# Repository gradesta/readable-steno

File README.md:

# readable-steno

[Discord link](https://discord.com/channels/136953735426473984/1390298469813452810)

Imagine if you had a steno keyboard where the keys could move on their own. This would allow you to read haptically in the same way you typed. And perhapse at up to hundres of words per minute. Far faster than braille. This is the idea of our project. 

So far we have a prototype with LED lights rather than solenoids. In the future, we will replace these LEDs with electromagnets which can trigger the keys to jump up at you.

# Tutorial to replicate
### Prerquisites
There are some dependencies you will have to install before following this tutorial, these include dependencies both for the firmware and pico-sdk:
```
sudo apt install cmake python3 build-essential gcc-arm-none-eabi libnewlib-arm-none-eabi libstdc++-arm-none-eabi-newlib
```
### Steps
1. Clone [the readable steno](https://github.com/gradesta/readable-steno#) and the [pico-sdk](https://github.com/raspberrypi/pico-sdk#) repositories: 
```
git clone git@github.com:gradesta/readable-steno.git
git clone git@github.com:raspberrypi/pico-sdk.git
```
2. Now we need to initiate the submodules, for pico-sdk as the tinyUsb module does not come installed in pico-sdk immediately:
```
cd pico-sdk
git submodule update --init
```

3. Before we can start building our project, we need a `dict.h` file, which the firmware expects to be present. To do this, we will use a .json steno dictionary. You can either use the same as us (typey-type-full.json) or add your own in its place. We will move to the `read_code` folder and run the translation script:
```
cd ../readable-steno/read_code
python3 translator.py <your_dict_name>.json
```
For example 
```
python3 translator.py typey-type-full.json
```
You should see a `dict.h` file now.

4. Next we will make a build folder and generate the necessary CMake files in it. If you are correctly following these steps, then the file paths should be the same:
```
mkdir build
cd build
cmake .. -DPICO_SDK_PATH=../../../pico-sdk
```

5. You should have several new files generated in the `build` folder. Now, just run:
```
make
```
And your firmware should be compiled.

6. After it is compiled a file called `read_code.uf2` will be in the `build` folder. This is the firmware for the board. To flash it, hold the reset button on the microcontroller while plugging it in. It should show up as a usb device. Now just drag the `read_code.uf2` file on it, wait while it flashes and you are done.

### Keep in mind
If you used the liatris  controller, then you cannot use GPIO 10 for the LEDs. In [this](https://github.com/gradesta/readable-steno/blob/main/dev_log/%235-11_08_2025-15_08_2025.md) dev-log we showed how we fixed it. The important thing is, not to forget to change the pin number in [led_driver.h](https://github.com/gradesta/readable-steno/blob/main/read_code/led_driver.h). 

## Testing
To actually test the software, you will need some kind of serial monitor, for exapmle `screen` and find the com port of the keyboard. In our case it was /dev/ttyACM0. Now you just run:
```
sudo screen /dev/ttyACM0 115200
```
And a serial monitor should show up where you can type a message to show on the keyboard (up to 3000 characters)

https://github.com/user-attachments/assets/7c71d7f1-2565-4da7-bef9-faf2f1da297b

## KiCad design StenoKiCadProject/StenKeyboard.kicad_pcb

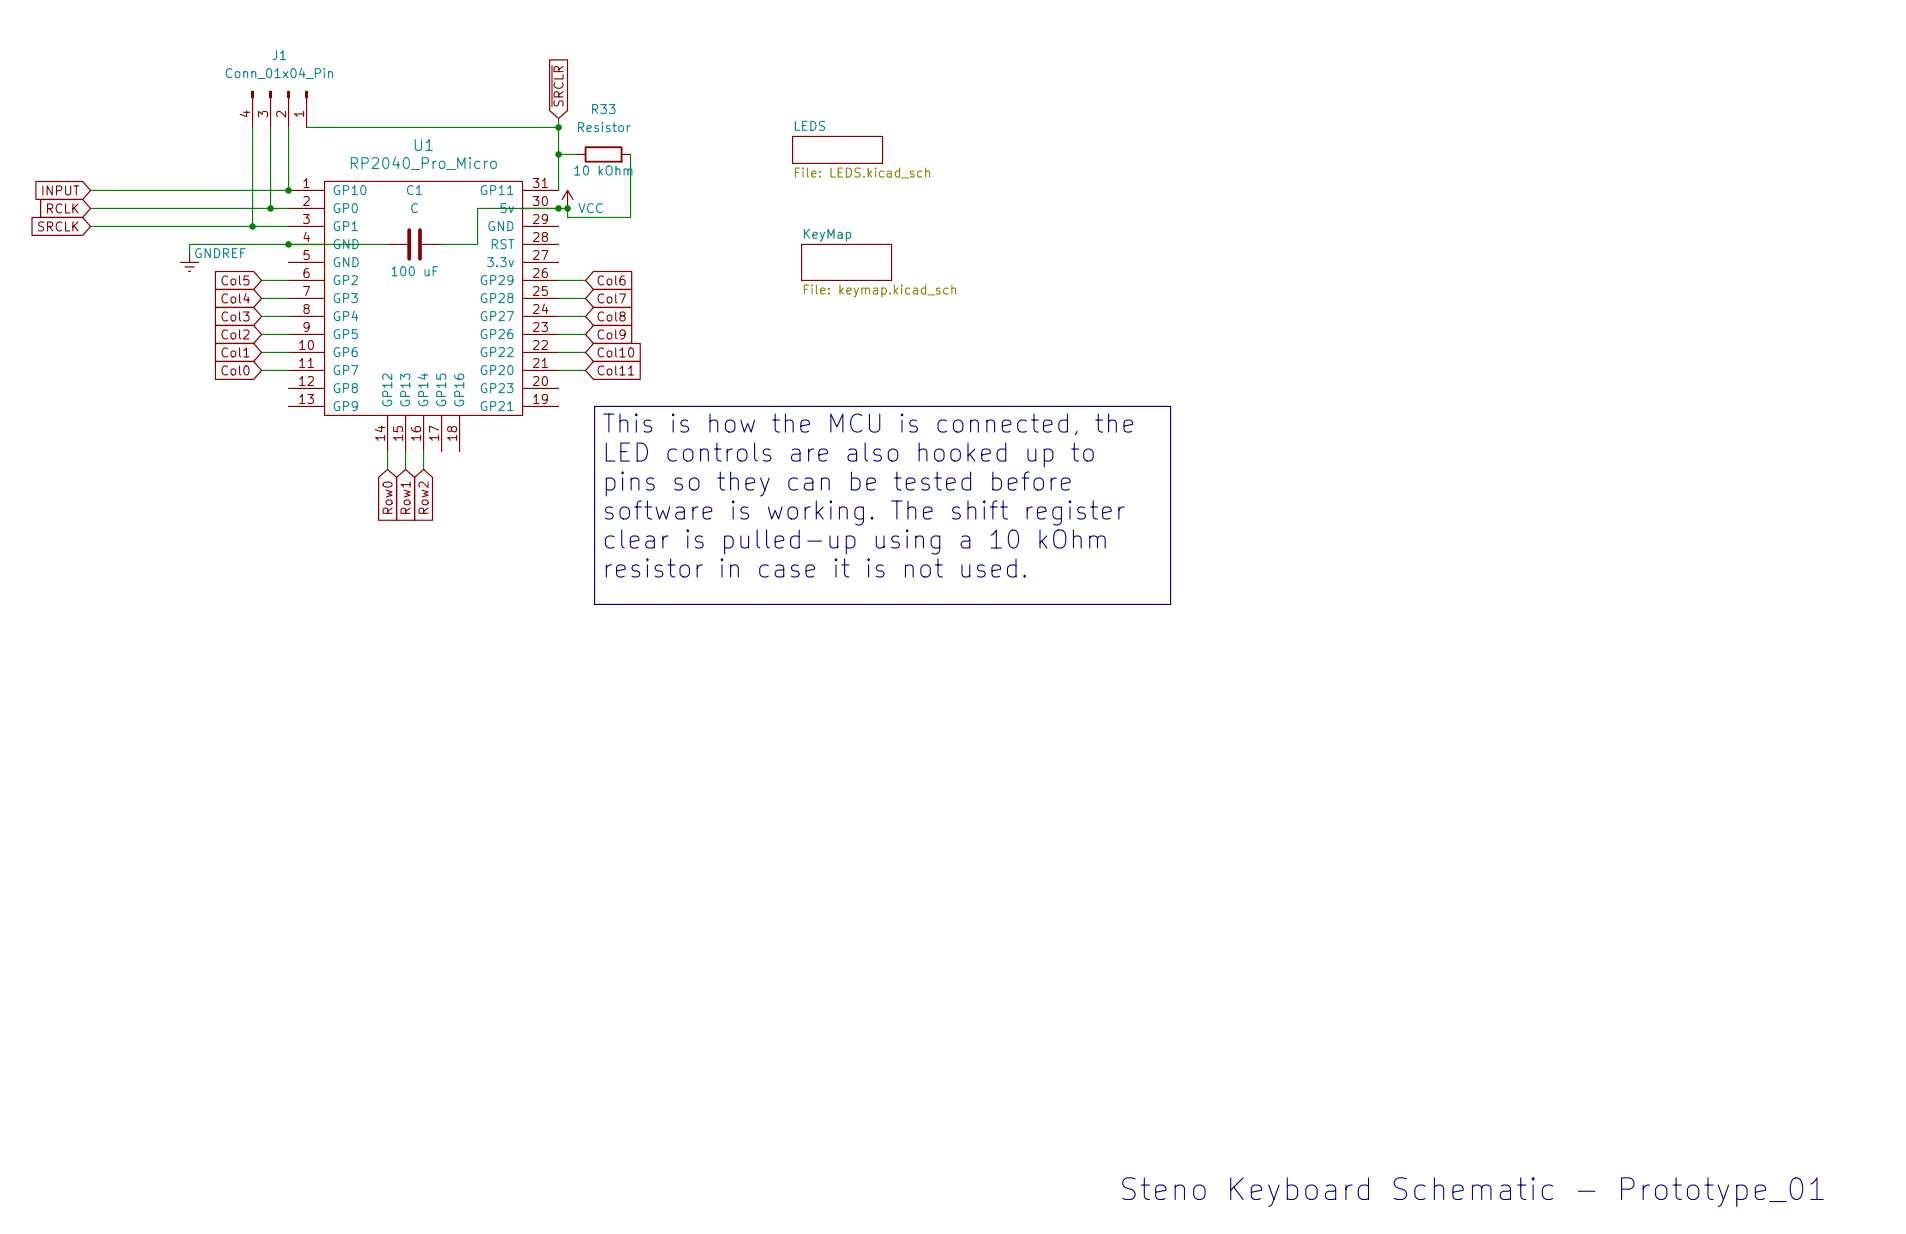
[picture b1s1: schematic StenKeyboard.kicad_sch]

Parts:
C1: C; C_1206_3216Metric
J1: Conn_01x04_Pin; PinHeader_1x04_P2.54mm_Vertical
R33: Resistor; R_1206_3216Metric
U1: RP2040_Pro_Micro

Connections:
Col0: U1.11 (GP7); also elsewhere on the board
Col1: U1.10 (GP6); also elsewhere on the board
Col2: U1.9 (GP5); also elsewhere on the board
Col3: U1.8 (GP4); also elsewhere on the board
Col4: U1.7 (GP3); also elsewhere on the board
Col5: U1.6 (GP2); also elsewhere on the board
Col6: U1.26 (GP29); also elsewhere on the board
Col7: U1.25 (GP28); also elsewhere on the board
Col8: U1.24 (GP27); also elsewhere on the board
Col9: U1.23 (GP26); also elsewhere on the board
Col10: U1.22 (GP22); also elsewhere on the board
Col11: U1.21 (GP20); also elsewhere on the board
GNDREF: C1.1, U1.4 (GND); also elsewhere on the board
INPUT: J1.2, U1.1 (GP10); also elsewhere on the board
RCLK: J1.3, U1.2 (GP0); also elsewhere on the board
Row0: U1.14 (GP12); also elsewhere on the board
Row1: U1.15 (GP13); also elsewhere on the board
Row2: U1.16 (GP14); also elsewhere on the board
SRCLK: J1.4, U1.3 (GP1); also elsewhere on the board
VCC: C1.2, R33.2, U1.30 (5v); also elsewhere on the board
~SRCLR: J1.1, R33.1, U1.31 (GP11); also elsewhere on the board

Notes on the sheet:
Steno Keyboard Schematic - Prototype_01
This is how the MCU is connected, the LED controls are also hooked up to pins so they can be tested before software is working. The shift register clear is pulled-up using a 10 kOhm resistor in case it is not used.

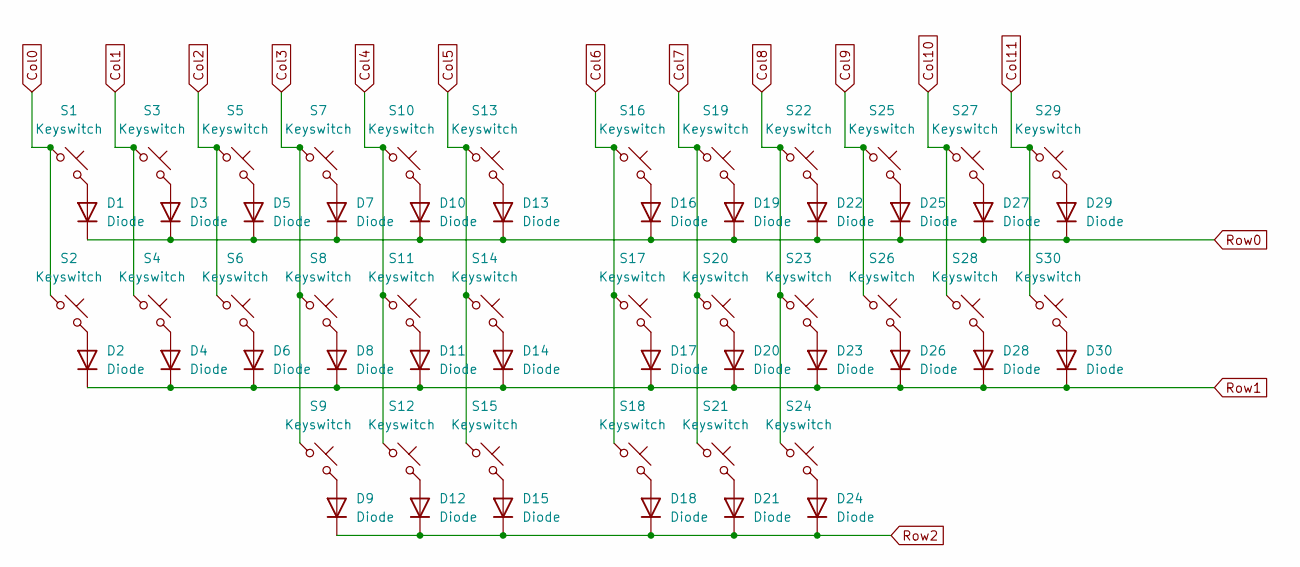
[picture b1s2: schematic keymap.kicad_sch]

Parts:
D1, D2, D3, D4, D5, D6, D7, D8, D9, D10, D11, D12, D13, D14, D15, D16, D17, D18, D19, D20, D21, D22, D23, D24, D25, D26, D27, D28, D29, D30: Diode; D_1206_3216Metric
S1, S2, S3, S4, S5, S6, S7, S8, S9, S10, S11, S12, S13, S14, S15, S16, S17, S18, S19, S20, S21, S22, S23, S24, S25, S26, S27, S28, S29, S30: Keyswitch; Hotswap_Choc_V1

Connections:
Col0: S1.1, S2.1; also elsewhere on the board
Col1: S3.1, S4.1; also elsewhere on the board
Col2: S5.1, S6.1; also elsewhere on the board
Col3: S7.1, S8.1, S9.1; also elsewhere on the board
Col4: S10.1, S11.1, S12.1; also elsewhere on the board
Col5: S13.1, S14.1, S15.1; also elsewhere on the board
Col6: S16.1, S17.1, S18.1; also elsewhere on the board
Col7: S19.1, S20.1, S21.1; also elsewhere on the board
Col8: S22.1, S23.1, S24.1; also elsewhere on the board
Col9: S25.1, S26.1; also elsewhere on the board
Col10: S27.1, S28.1; also elsewhere on the board
Col11: S29.1, S30.1; also elsewhere on the board
unnamed: D1.2 (A), S1.2
unnamed: D2.2 (A), S2.2
unnamed: D3.2 (A), S3.2
unnamed: D4.2 (A), S4.2
unnamed: D5.2 (A), S5.2
unnamed: D6.2 (A), S6.2
unnamed: D7.2 (A), S7.2
unnamed: D8.2 (A), S8.2
unnamed: D9.2 (A), S9.2
unnamed: D10.2 (A), S10.2
unnamed: D11.2 (A), S11.2
unnamed: D12.2 (A), S12.2
unnamed: D13.2 (A), S13.2
unnamed: D14.2 (A), S14.2
unnamed: D15.2 (A), S15.2
unnamed: D16.2 (A), S16.2
unnamed: D17.2 (A), S17.2
unnamed: D18.2 (A), S18.2
unnamed: D19.2 (A), S19.2
unnamed: D20.2 (A), S20.2
unnamed: D21.2 (A), S21.2
unnamed: D22.2 (A), S22.2
unnamed: D23.2 (A), S23.2
unnamed: D24.2 (A), S24.2
unnamed: D25.2 (A), S25.2
unnamed: D26.2 (A), S26.2
unnamed: D27.2 (A), S27.2
unnamed: D28.2 (A), S28.2
unnamed: D29.2 (A), S29.2
unnamed: D30.2 (A), S30.2
Row0: D1.1 (K), D3.1 (K), D5.1 (K), D7.1 (K), D10.1 (K), D13.1 (K), D16.1 (K), D19.1 (K), D22.1 (K), D25.1 (K), D27.1 (K), D29.1 (K); also elsewhere on the board
Row1: D2.1 (K), D4.1 (K), D6.1 (K), D8.1 (K), D11.1 (K), D14.1 (K), D17.1 (K), D20.1 (K), D23.1 (K), D26.1 (K), D28.1 (K), D30.1 (K); also elsewhere on the board
Row2: D9.1 (K), D12.1 (K), D15.1 (K), D18.1 (K), D21.1 (K), D24.1 (K); also elsewhere on the board

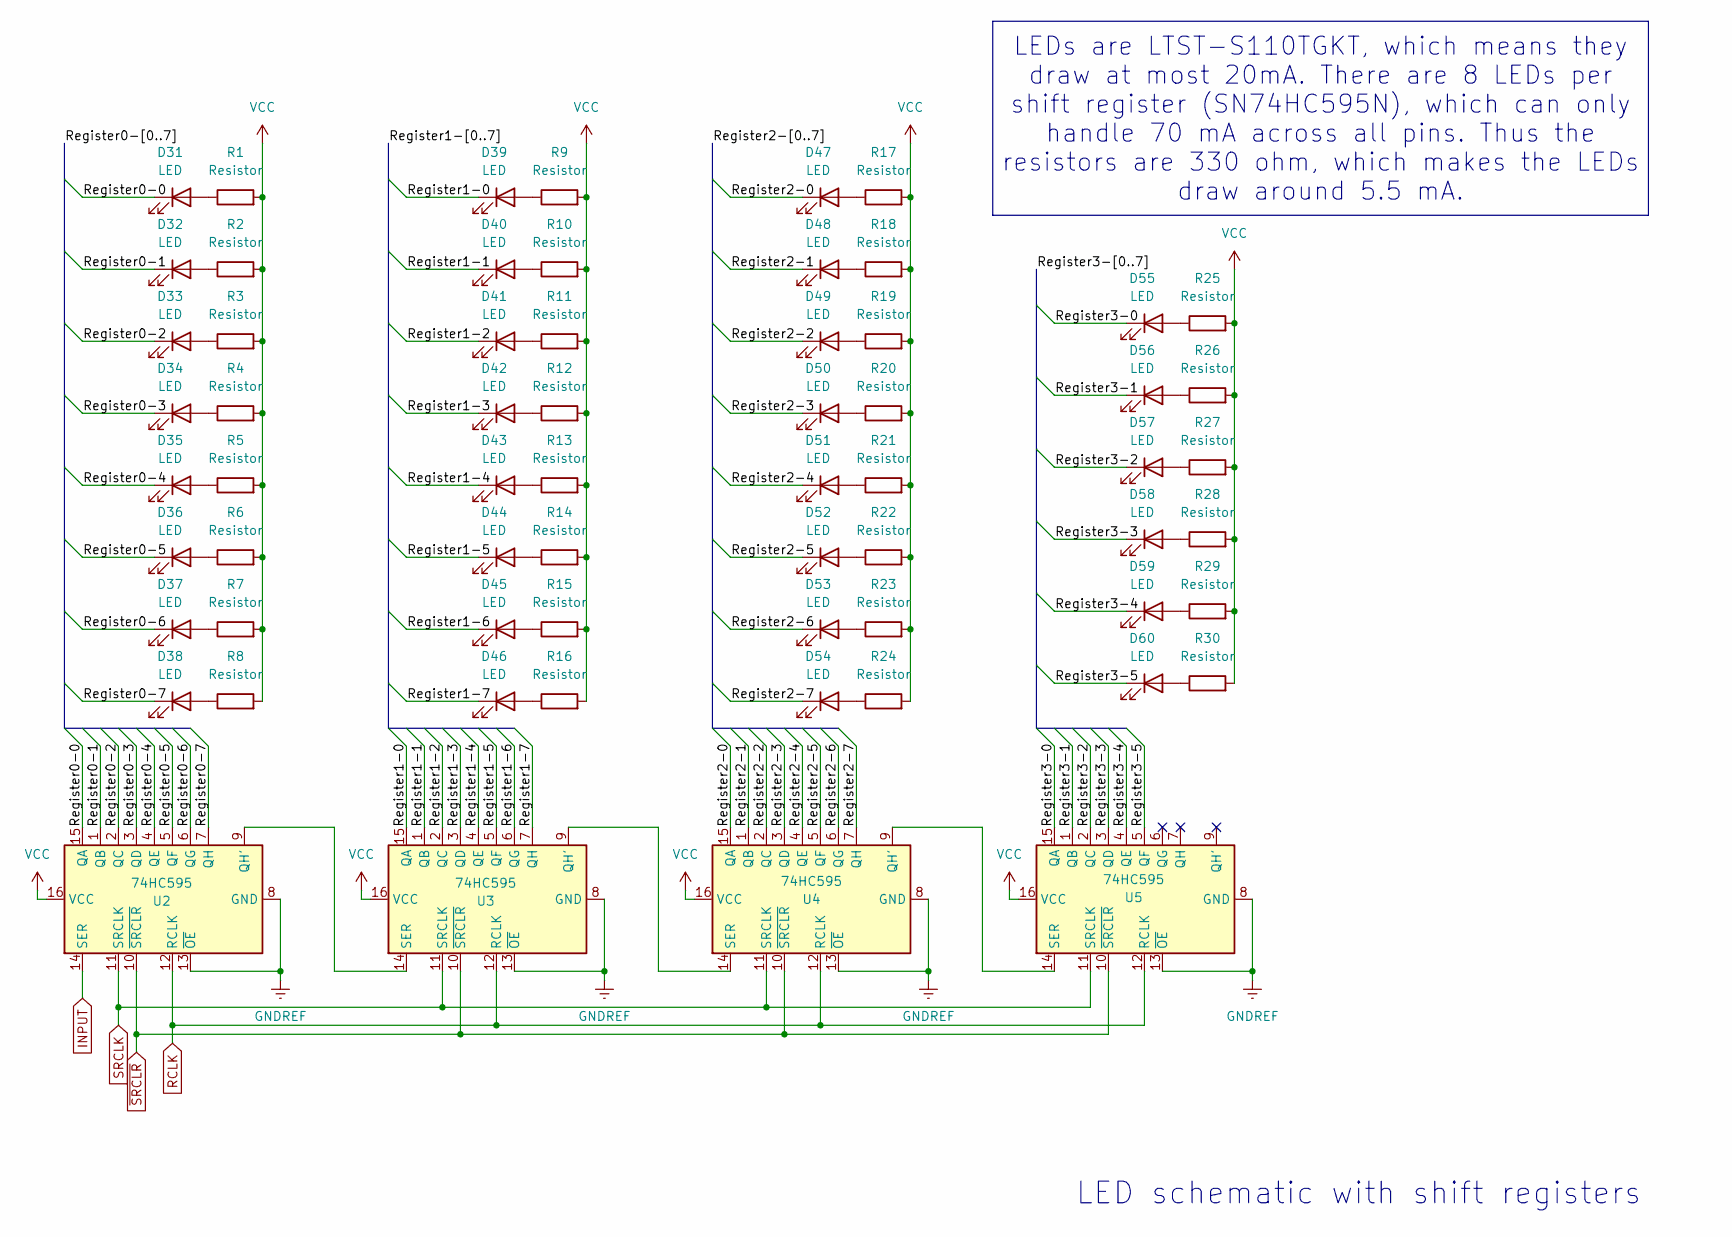
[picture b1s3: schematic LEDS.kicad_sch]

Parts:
D31, D32, D33, D34, D35, D36, D37, D38, D39, D40, D41, D42, D43, D44, D45, D46, D47, D48, D49, D50, D51, D52, D53, D54, D55, D56, D57, D58, D59, D60: LED; LED_1206_3216Metric
R1, R2, R3, R4, R5, R6, R7, R8, R9, R10, R11, R12, R13, R14, R15, R16, R17, R18, R19, R20, R21, R22, R23, R24, R25, R26, R27, R28, R29, R30: Resistor; R_1206_3216Metric
U2, U3, U4, U5: 74HC595; DIP-16_W7.62mm

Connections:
/LEDS/Register0-0: D31.1 (K), U2.15 (QA)
/LEDS/Register0-1: D32.1 (K), U2.1 (QB)
/LEDS/Register0-2: D33.1 (K), U2.2 (QC)
/LEDS/Register0-3: D34.1 (K), U2.3 (QD)
/LEDS/Register0-4: D35.1 (K), U2.4 (QE)
/LEDS/Register0-5: D36.1 (K), U2.5 (QF)
/LEDS/Register0-6: D37.1 (K), U2.6 (QG)
/LEDS/Register0-7: D38.1 (K), U2.7 (QH)
/LEDS/Register1-0: D39.1 (K), U3.15 (QA)
/LEDS/Register1-1: D40.1 (K), U3.1 (QB)
/LEDS/Register1-2: D41.1 (K), U3.2 (QC)
/LEDS/Register1-3: D42.1 (K), U3.3 (QD)
/LEDS/Register1-4: D43.1 (K), U3.4 (QE)
/LEDS/Register1-5: D44.1 (K), U3.5 (QF)
/LEDS/Register1-6: D45.1 (K), U3.6 (QG)
/LEDS/Register1-7: D46.1 (K), U3.7 (QH)
/LEDS/Register2-0: D47.1 (K), U4.15 (QA)
/LEDS/Register2-1: D48.1 (K), U4.1 (QB)
/LEDS/Register2-2: D49.1 (K), U4.2 (QC)
/LEDS/Register2-3: D50.1 (K), U4.3 (QD)
/LEDS/Register2-4: D51.1 (K), U4.4 (QE)
/LEDS/Register2-5: D52.1 (K), U4.5 (QF)
/LEDS/Register2-6: D53.1 (K), U4.6 (QG)
/LEDS/Register2-7: D54.1 (K), U4.7 (QH)
/LEDS/Register3-0: D55.1 (K), U5.15 (QA)
/LEDS/Register3-1: D56.1 (K), U5.1 (QB)
/LEDS/Register3-2: D57.1 (K), U5.2 (QC)
/LEDS/Register3-3: D58.1 (K), U5.3 (QD)
/LEDS/Register3-4: D59.1 (K), U5.4 (QE)
/LEDS/Register3-5: D60.1 (K), U5.5 (QF)
GNDREF: U2.8 (GND), U2.13 (~OE), U3.8 (GND), U3.13 (~OE), U4.8 (GND), U4.13 (~OE), U5.8 (GND), U5.13 (~OE); also elsewhere on the board
INPUT: U2.14 (SER); also elsewhere on the board
unnamed: D31.2 (A), R1.1
unnamed: D32.2 (A), R2.1
unnamed: D33.2 (A), R3.1
unnamed: D34.2 (A), R4.1
unnamed: D35.2 (A), R5.1
unnamed: D36.2 (A), R6.1
unnamed: D37.2 (A), R7.1
unnamed: D38.2 (A), R8.1
unnamed: D39.2 (A), R9.1
unnamed: D40.2 (A), R10.1
unnamed: D41.2 (A), R11.1
unnamed: D42.2 (A), R12.1
unnamed: D43.2 (A), R13.1
unnamed: D44.2 (A), R14.1
unnamed: D45.2 (A), R15.1
unnamed: D46.2 (A), R16.1
unnamed: D47.2 (A), R17.1
unnamed: D48.2 (A), R18.1
unnamed: D49.2 (A), R19.1
unnamed: D50.2 (A), R20.1
unnamed: D51.2 (A), R21.1
unnamed: D52.2 (A), R22.1
unnamed: D53.2 (A), R23.1
unnamed: D54.2 (A), R24.1
unnamed: D55.2 (A), R25.1
unnamed: D56.2 (A), R26.1
unnamed: D57.2 (A), R27.1
unnamed: D58.2 (A), R28.1
unnamed: D59.2 (A), R29.1
unnamed: D60.2 (A), R30.1
unnamed: U2.9 (QH'), U3.14 (SER)
unnamed: U3.9 (QH'), U4.14 (SER)
unnamed: U4.9 (QH'), U5.14 (SER)
RCLK: U2.12 (RCLK), U3.12 (RCLK), U4.12 (RCLK), U5.12 (RCLK); also elsewhere on the board
SRCLK: U2.11 (SRCLK), U3.11 (SRCLK), U4.11 (SRCLK), U5.11 (SRCLK); also elsewhere on the board
VCC: R1.2, R2.2, R3.2, R4.2, R5.2, R6.2, R7.2, R8.2, R9.2, R10.2, R11.2, R12.2, R13.2, R14.2, R15.2, R16.2, R17.2, R18.2, R19.2, R20.2, R21.2, R22.2, R23.2, R24.2, R25.2, R26.2, R27.2, R28.2, R29.2, R30.2, U2.16 (VCC), U3.16 (VCC), U4.16 (VCC), U5.16 (VCC); also elsewhere on the board
~SRCLR: U2.10 (~SRCLR), U3.10 (~SRCLR), U4.10 (~SRCLR), U5.10 (~SRCLR); also elsewhere on the board

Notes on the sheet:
LED schematic with shift registers
LEDs are LTST-S110TGKT, which means they draw at most 20mA. There are 8 LEDs per shift register (SN74HC595N), which can only handle 70 mA across all pins. Thus the resistors are 330 ohm, which makes the LEDs draw around 5.5 mA.

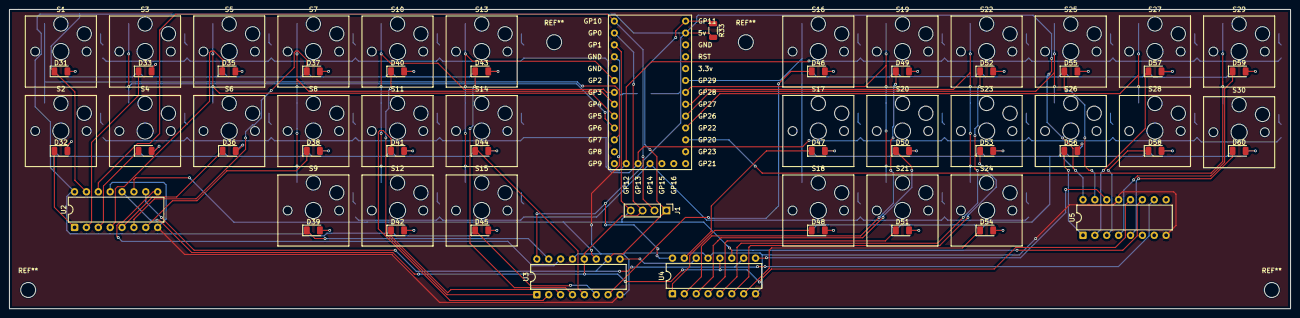
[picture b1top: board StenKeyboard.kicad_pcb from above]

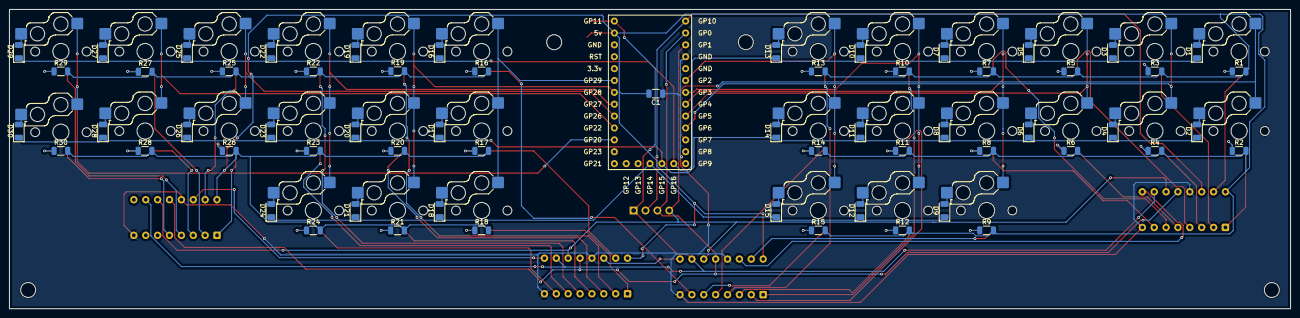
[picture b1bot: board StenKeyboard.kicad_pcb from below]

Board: 2 copper layers, 274.0 x 64.0 mm, 128 parts (61 on the bottom side), 114 nets.

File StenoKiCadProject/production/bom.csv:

Designator,Footprint,Quantity,Value,LCSC Part #
C1,1206,1,C,
"D1, D10, D11, D12, D13, D14, D15, D16, D17, D18, D19, D2, D20, D21, D22, D23, D24, D25, D26, D27, D28, D29, D3, D30, D4, D5, D6, D7, D8, D9",1206,30,Diode,
"D31, D32, D33, D34, D35, D36, D37, D38, D39, D40, D41, D42, D43, D44, D45, D46, D47, D48, D49, D50, D51, D52, D53, D54, D55, D56, D57, D58, D59, D60",1206,30,LED,
J1,PinHeader_1x04_P2.54mm_Vertical,1,Conn_01x04_Pin,
"R1, R10, R11, R12, R13, R14, R15, R16, R17, R18, R19, R2, R20, R21, R22, R23, R24, R25, R26, R27, R28, R29, R3, R30, R33, R4, R5, R6, R7, R8, R9",1206,31,Resistor,
"S1, S10, S11, S12, S13, S14, S15, S16, S17, S18, S19, S2, S20, S21, S22, S23, S24, S25, S26, S27, S28, S29, S3, S30, S4, S5, S6, S7, S8, S9",Hotswap_Choc_V1,30,Keyswitch,
U1,RP2040_Pro_Micro,1,RP2040_Pro_Micro,
"U2, U3, U4, U5",DIP-16_W7.62mm,4,74HC595,

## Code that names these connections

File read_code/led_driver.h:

#ifndef LED_DRIVER_H
#define LED_DRIVER_H

#include <stdint.h>
#include <sys/types.h>

//#define LED_PIN 10
#define LED_PIN 10 //Input pin for the shift registers, IMPORTANT: in case of liatris controller you have to change the pin and hardwire it there
                   // I used pin 21
#define SRCLK 1 //Shift register clock, used when shifting bits in 
#define RCLK 0 //Clock, used when using parallel output of registers

//#define SRCLR //Used to clear shift registers, but because of the wiring it turns on all leds.
                //Pulled high using a resistor, can be used, but not necessary

#define SIZE 30 //Number of leds

void setup(); //Called before using leds, to initialize the gpio pins
void clear(); //Turns off all leds
void send(uint8_t *leds, size_t size); //Lights up leds based on the indices provided using <leds>
void test(); //Test whether all leds are working

#endif

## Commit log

2025-07-09 feat: Created dev_log folder
2025-07-09 feat: Written first dev_log
2025-07-09 Added pictures to dev_log
2025-07-09 feat: Uploaded gerber file
2025-07-09 fix: Added missing component to material list
2025-07-09 fix: Added MCU info
2025-07-17 Added new dev log and config file
2025-07-17 Update 14_07_2025-18_07_2025.md | Added pictures
2025-07-23 Added new dev log and updated old devlog names
2025-08-08 Added dev log and code for leds
2025-08-17 Updated git ignore
2025-08-17 Updated read code to use serial communication, fixed bugs in translator.py
2025-08-17 New dev log
2025-08-29 New dev log and worked on communication
2025-09-24 Finished code for reading
2025-09-24 Added devlog
2025-09-24 Added video to dev log
2025-09-24 Tiny code update
2025-10-08 Added tutorial to setup software development enviroment and edited translator.py, CMakeLists.txt and main.c for simpler setup
2025-10-08 Added prerequisites to tutorial
2025-10-08 Edited include path in CMakeLists.txt
2025-10-08 Revise prerequisites for tutorial dependencies
    Updated prerequisites section to include additional dependencies and installation instructions.
2025-10-08 Added testing paragraph in tutorial
2025-10-08 Added video to tutorial
2025-10-11 Updated .gitignore, updated README and added gerber for testing board for coils
2026-01-27 Added KiCAD project files
